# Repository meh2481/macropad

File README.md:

# macropad
Just a 6-key macropad but mine is better because RGB amirite

Archived as there are too many problems:
- Need a resister per RGB input, not one per output, as constant current across the RGBLED distorts the color otherwise. That's a lot of SMD components.
- The RPi Pico has a limited number of PWM units, not enough for running all of the RGBLEDs, and they were hooked up incorrectly anyway.
- Idea was ditched in favor of streamdekc instead.

# Materials
Parts used (Can easily be subbed for something similar):
- 1x [Raspberry Pi Pico](https://www.raspberrypi.com/products/raspberry-pi-pico/)
- 1x [I2C OLED Display](https://www.adafruit.com/product/4440)
- 6x [Kailh Choc Switch](http://www.kailh.com/en/Products/Ks/CS/) (Linear or clicky with spring mechanism removed)
- 6x [Clear Kailh CHOC Keycaps](https://www.adafruit.com/product/5110)
- 6x [Diffused Rectangular RGB LEDs (5 x 2.5mm)](https://www.adafruit.com/product/2739) or something that fits in the Kailh holes
- MicroUSB cable
- 4x [M3-ish size plastic screws](https://www.amazon.com/dp/B00GDYDCC0) or similar

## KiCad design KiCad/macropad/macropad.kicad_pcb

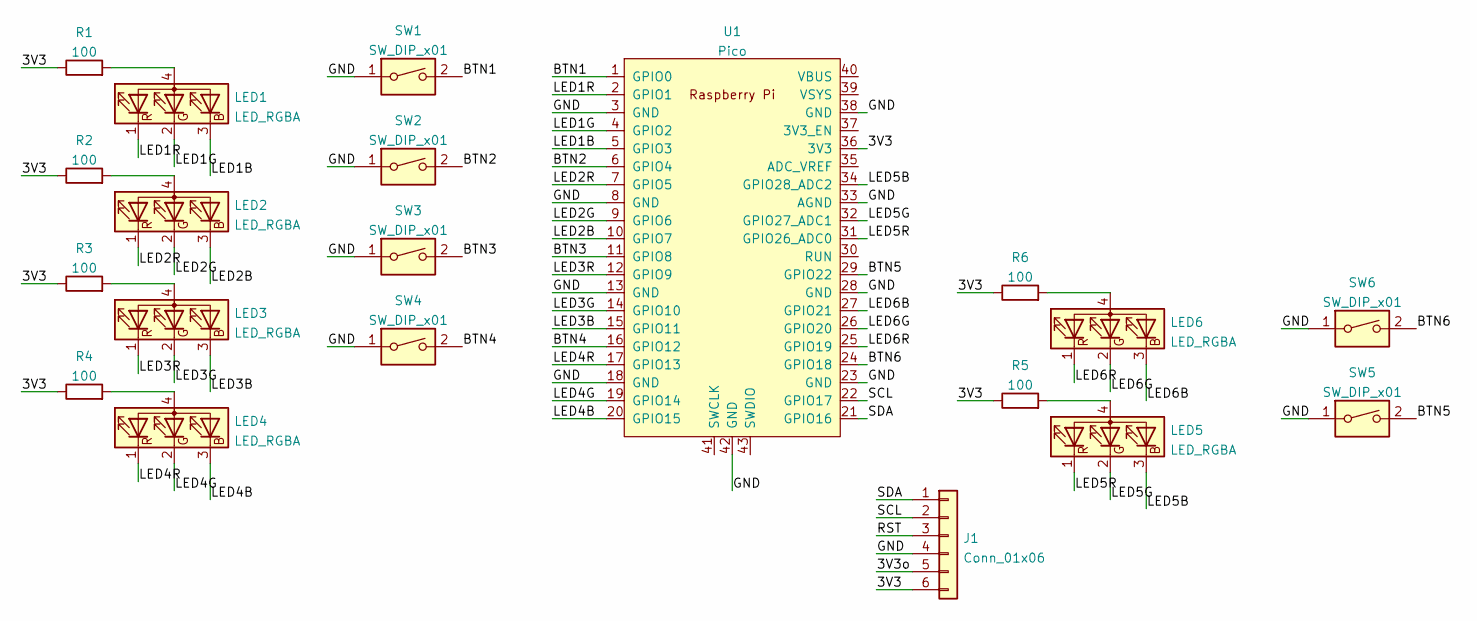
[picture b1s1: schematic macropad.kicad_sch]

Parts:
J1: Conn_01x06; PinHeader_1x06_P2.54mm_Vertical
LED1, LED2, LED3, LED4, LED5, LED6: LED_RGBA; 1.5mmRGBALED
R1, R2, R3, R4, R5, R6: 100; R_Axial_DIN0309_L9.0mm_D3.2mm_P12.70mm_Horizontal; LCSC C25076
SW1, SW2, SW3, SW4, SW5, SW6: SW_DIP_x01; Kailh_socket_PG1350
U1: Pico; RPi_Pico_SMD

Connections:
/3V3: J1.6, R1.1, R2.1, R3.1, R4.1, R5.1, R6.1, U1.36 (3V3)
/3V3o: J1.5
/BTN1: SW1.2, U1.1 (GPIO0)
/BTN2: SW2.2, U1.6 (GPIO4)
/BTN3: SW3.2, U1.11 (GPIO8)
/BTN4: SW4.2, U1.16 (GPIO12)
/BTN5: SW5.2, U1.29 (GPIO22)
/BTN6: SW6.2, U1.24 (GPIO18)
/GND: J1.4, SW1.1, SW2.1, SW3.1, SW4.1, SW5.1, SW6.1, U1.3 (GND), U1.8 (GND), U1.13 (GND), U1.18 (GND), U1.23 (GND), U1.28 (GND), U1.33 (AGND), U1.38 (GND), U1.42 (GND)
/LED1B: LED1.3 (BK), U1.5 (GPIO3)
/LED1G: LED1.2 (GK), U1.4 (GPIO2)
/LED1R: LED1.1 (RK), U1.2 (GPIO1)
/LED2B: LED2.3 (BK), U1.10 (GPIO7)
/LED2G: LED2.2 (GK), U1.9 (GPIO6)
/LED2R: LED2.1 (RK), U1.7 (GPIO5)
/LED3B: LED3.3 (BK), U1.15 (GPIO11)
/LED3G: LED3.2 (GK), U1.14 (GPIO10)
/LED3R: LED3.1 (RK), U1.12 (GPIO9)
/LED4B: LED4.3 (BK), U1.20 (GPIO15)
/LED4G: LED4.2 (GK), U1.19 (GPIO14)
/LED4R: LED4.1 (RK), U1.17 (GPIO13)
/LED5B: LED5.3 (BK), U1.34 (GPIO28_ADC2)
/LED5G: LED5.2 (GK), U1.32 (GPIO27_ADC1)
/LED5R: LED5.1 (RK), U1.31 (GPIO26_ADC0)
/LED6B: LED6.3 (BK), U1.27 (GPIO21)
/LED6G: LED6.2 (GK), U1.26 (GPIO20)
/LED6R: LED6.1 (RK), U1.25 (GPIO19)
/RST: J1.3
/SCL: J1.2, U1.22 (GPIO17)
/SDA: J1.1, U1.21 (GPIO16)
unnamed: LED1.4 (A), R1.2
unnamed: LED2.4 (A), R2.2
unnamed: LED3.4 (A), R3.2
unnamed: LED4.4 (A), R4.2
unnamed: LED5.4 (A), R5.2
unnamed: LED6.4 (A), R6.2

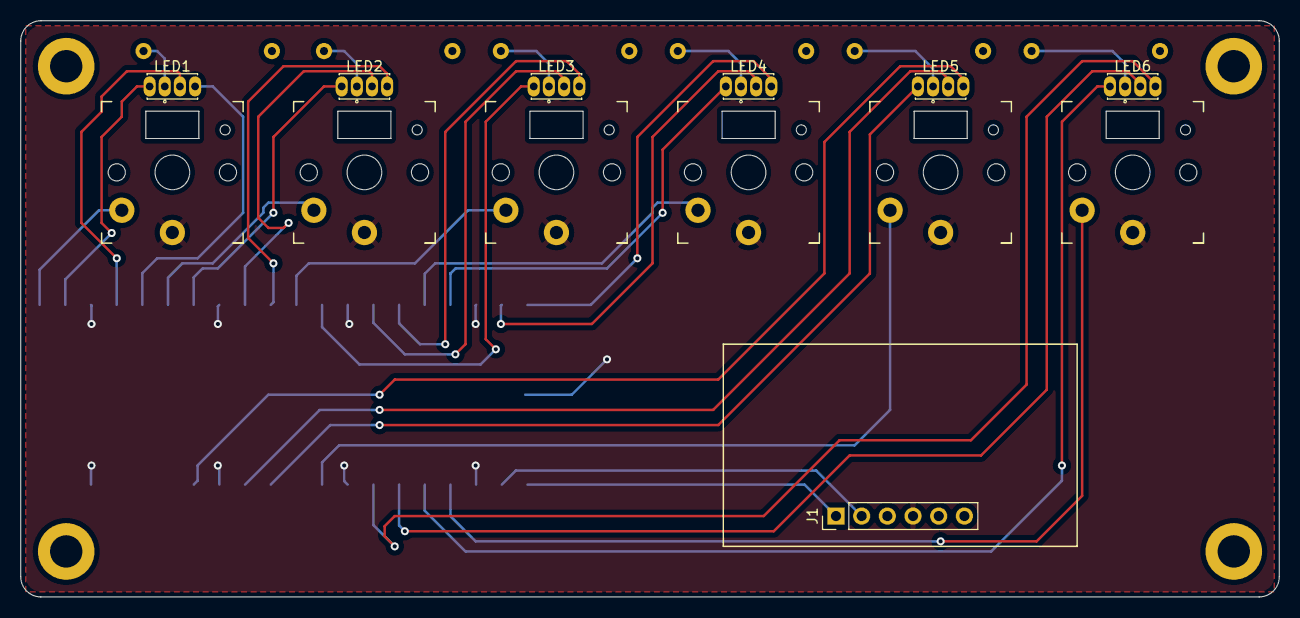
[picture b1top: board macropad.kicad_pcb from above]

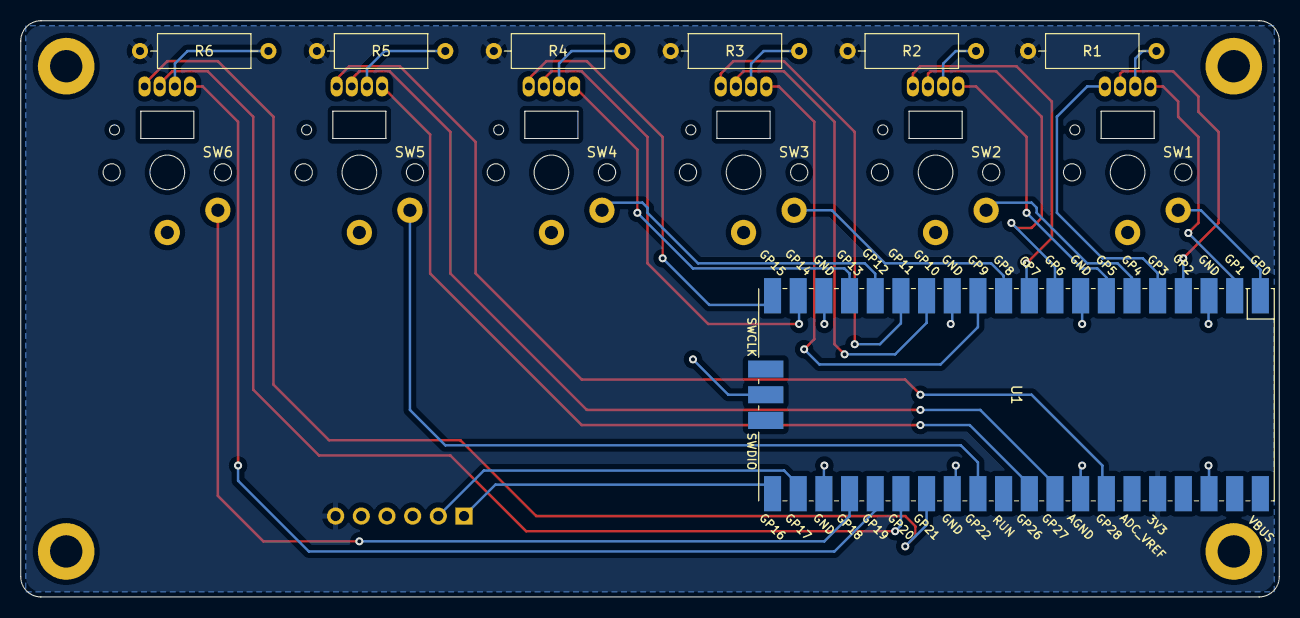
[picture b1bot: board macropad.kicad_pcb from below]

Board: 2 copper layers, 124.5 x 57.0 mm, 20 parts (7 on the bottom side), 34 nets.

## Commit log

2022-03-31 Migrate folders, start kicad project
2022-04-01 Initial wiring
2022-04-01 Settings for gerber export
2022-04-01 Add BOM to README
2022-04-02 add PWMs, fix led flicker
2022-04-02 Ideal world
2022-04-02 real world
2022-04-02 alternate pinouts that have better PWMs
2022-04-21 Use THT resistors, correct Kailh key layout, giving up on this project for now in favor of streamdekc
2022-04-21 Archiving project
